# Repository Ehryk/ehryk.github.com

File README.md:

ehryk.github.com
================

This is my github pages repo, viewable at [ehryk.github.io](http://ehryk.github.io). It also has some setup files that I sync between various computers, most notably git and bash aliases.

**Github Pages (/, /js, /css, /img)**

 - xkcd 1288 Substitutions Bookmarklet

**/linux && /git**

These are the settings I sync between various computers. Update Config.bat for windows, update-config.sh for linux.

**/rainmeter**

Custom Rainmeter skins for GPU and CPU temps, etc.

**/brian**

Brian's Stuff. See more at [Dr. Bird.org](http://www.drbird.org/)

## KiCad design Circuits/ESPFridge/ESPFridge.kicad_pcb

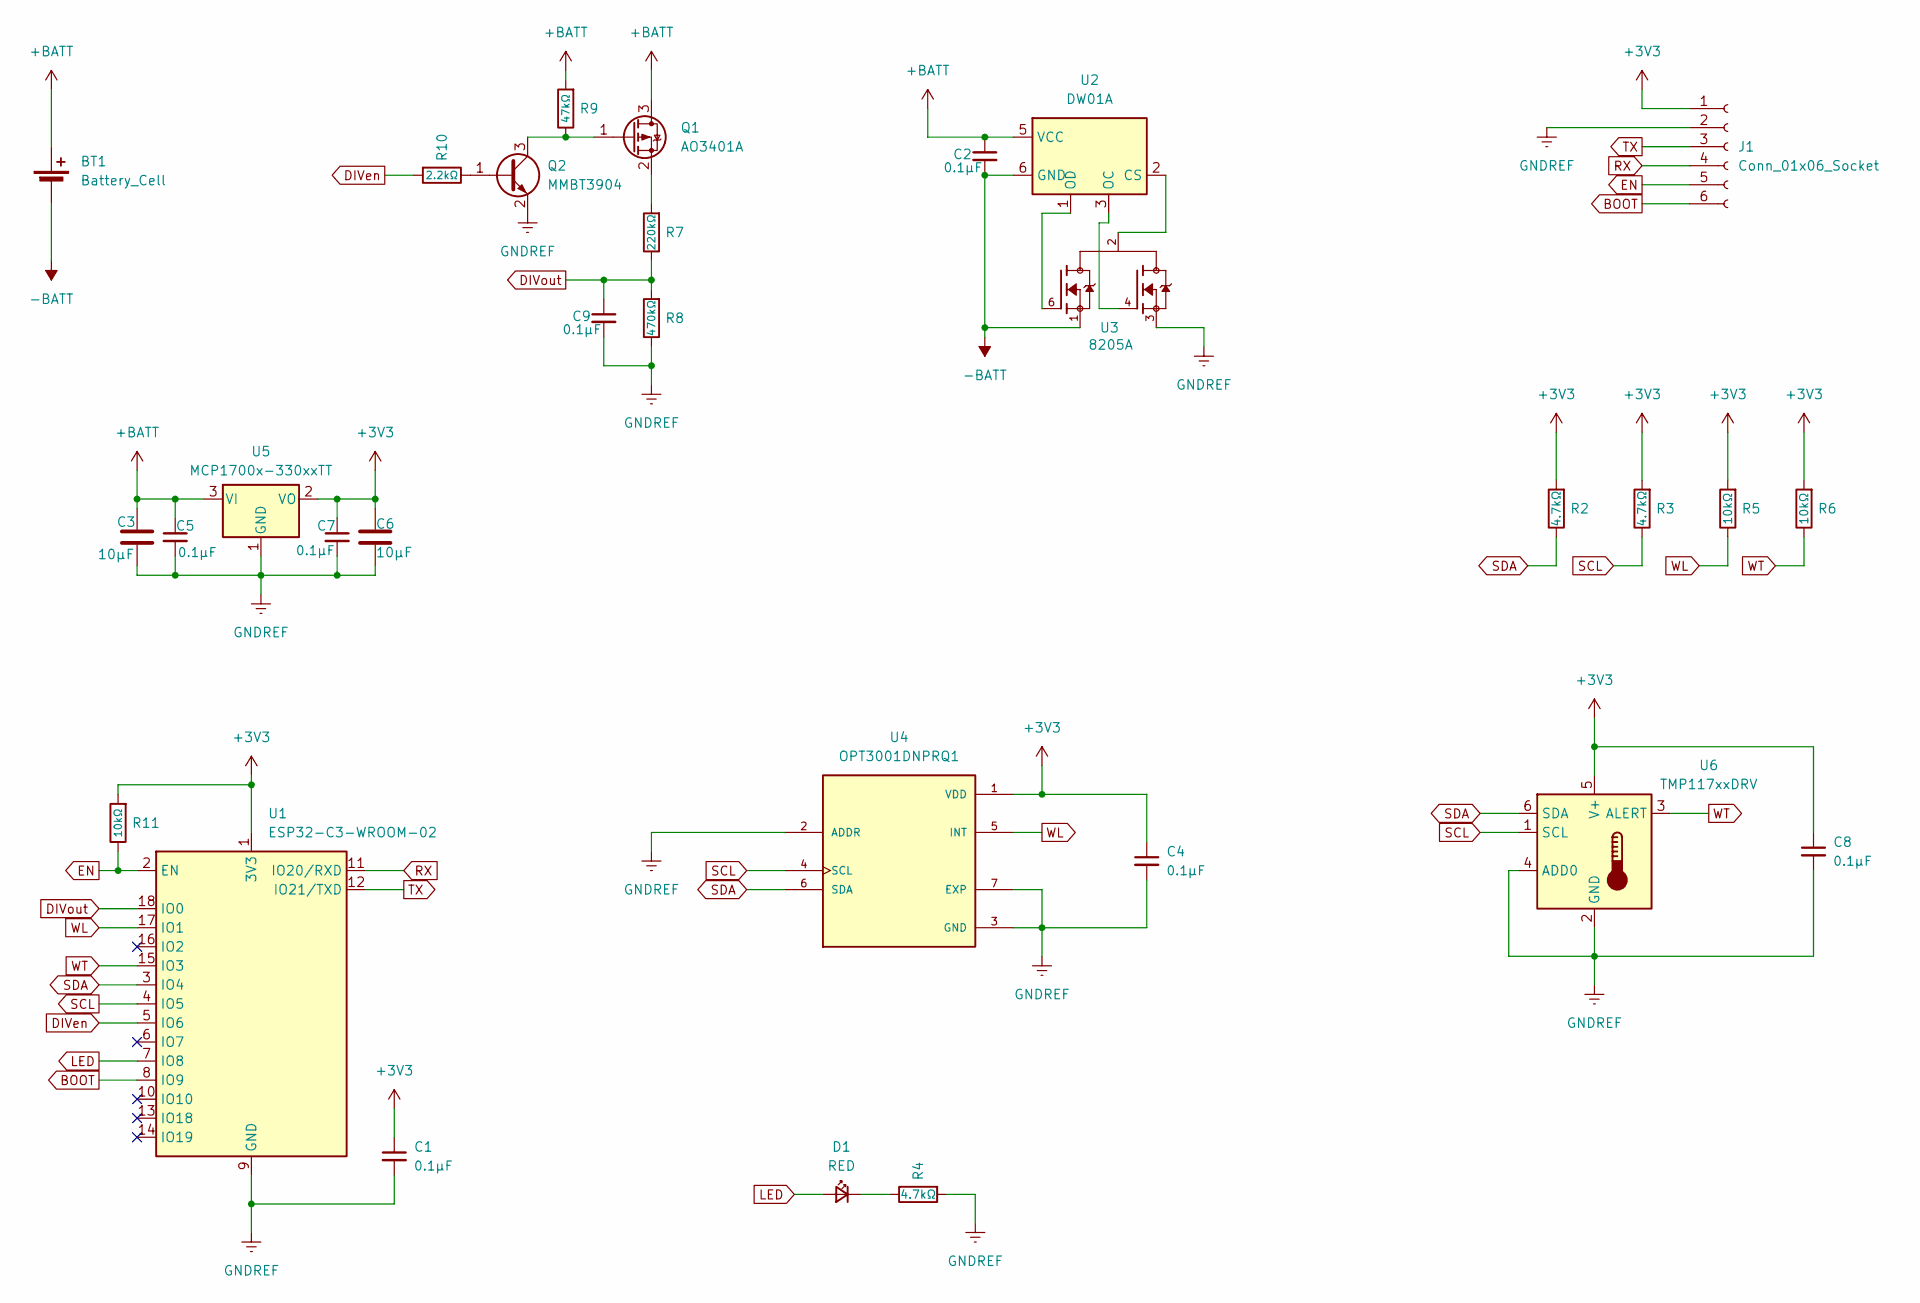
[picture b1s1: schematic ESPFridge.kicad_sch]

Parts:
BT1: Battery_Cell; Keystone_1043
C1, C2, C4, C5, C7, C8, C9: 0.1µF; C_1206_3216Metric_Pad1.33x1.80mm_HandSolder
C3, C6: 10µF; C_1210_3225Metric_Pad1.33x2.70mm_HandSolder
D1: RED; LED_0805_2012Metric_Pad1.15x1.40mm_HandSolder
J1: Conn_01x06_Socket; PinSocket_1x06_P2.00mm_Vertical_SMD_Pin1Left
Q1: AO3401A; SOT-23
Q2: MMBT3904; SOT-23
R2, R3, R4: 4.7kΩ; R_0805_2012Metric_Pad1.20x1.40mm_HandSolder
R5, R6, R11: 10kΩ; R_0805_2012Metric_Pad1.20x1.40mm_HandSolder
R7: 220kΩ; R_0805_2012Metric_Pad1.20x1.40mm_HandSolder
R8: 470kΩ; R_0805_2012Metric_Pad1.20x1.40mm_HandSolder
R9: 47kΩ; R_0805_2012Metric_Pad1.20x1.40mm_HandSolder
R10: 2.2kΩ; R_0805_2012Metric_Pad1.20x1.40mm_HandSolder
U1: ESP32-C3-WROOM-02
U2: DW01A; SOT-23-6
U3: 8205A; SOT95P285X140-6N; PARTREV NA
U4: OPT3001DNPRQ1; SON65P200X200X65-7N; PARTREV 01/2018
U5: MCP1700x-330xxTT; SOT-23
U6: TMP117xxDRV; WSON-6-1EP_2x2mm_P0.65mm_EP1x1.6mm

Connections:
+3V3: C1.1, C4.1, C6.1, C7.1, C8.1, J1.1, R2.2, R3.2, R5.2, R6.2, R11.2, U1.1 (3V3), U4.1 (VDD), U5.2 (VO), U6.5 (V+)
+BATT: BT1.P (+), C2.1, C3.1, C5.1, Q1.3 (D), R9.2, U2.5 (VCC), U5.3 (VI)
-BATT: BT1.N (-), C2.2, U2.6 (GND), U3.1
BOOT: J1.6, U1.8 (IO9)
DIVen: R10.2, U1.5 (IO6)
DIVout: C9.1, R7.1, R8.2, U1.18 (IO0)
EN: J1.5, R11.1, U1.2 (EN)
GNDREF: C1.2, C3.2, C4.2, C5.2, C6.2, C7.2, C8.2, C9.2, J1.2, Q2.2 (E), R4.2, R8.1, U1.9 (GND), U1.19 (GND), U3.3, U4.2 (ADDR), U4.3 (GND), U4.7 (EXP), U5.1 (GND), U6.2 (GND), U6.4 (ADD0)
LED: D1.2 (A), U1.7 (IO8)
unnamed: D1.1 (K), R4.1
unnamed: Q1.1 (G), Q2.3 (C), R9.1
unnamed: Q1.2 (S), R7.2
unnamed: Q2.1 (B), R10.1
unnamed: U2.2 (CS), U3.2, U3.5
unnamed: U2.3 (OC), U3.4
unnamed: U2.1 (OD), U3.6
RX: J1.4, U1.11 (IO20/RXD)
SCL: R3.1, U1.4 (IO5), U4.4 (SCL), U6.1 (SCL)
SDA: R2.1, U1.3 (IO4), U4.6 (SDA), U6.6 (SDA)
TX: J1.3, U1.12 (IO21/TXD)
WL: R5.1, U1.17 (IO1), U4.5 (INT)
WT: R6.1, U1.15 (IO3), U6.3 (ALERT)

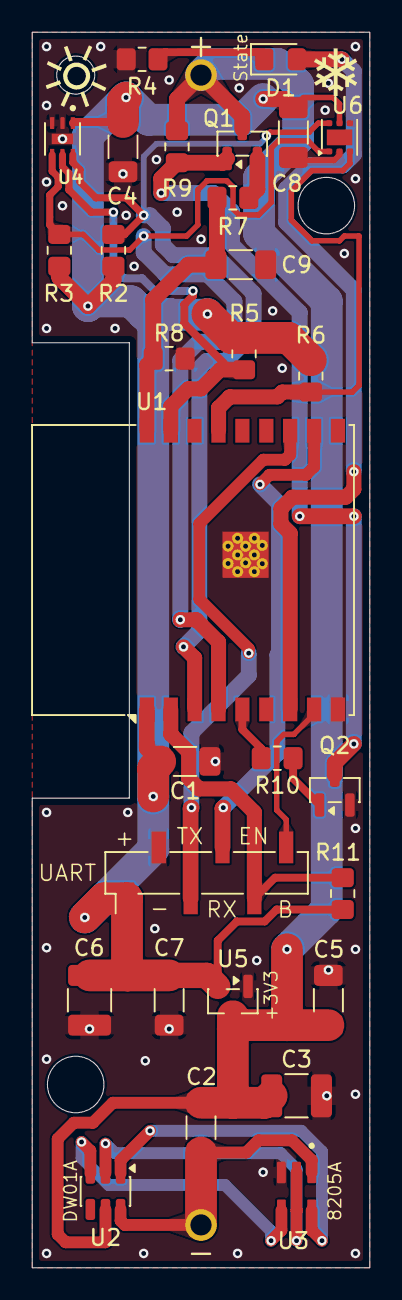
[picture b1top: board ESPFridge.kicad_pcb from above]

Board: 2 copper layers, 21.2 x 77.6 mm, 30 parts (1 on the bottom side), 22 nets.

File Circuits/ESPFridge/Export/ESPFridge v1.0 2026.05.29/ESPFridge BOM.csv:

"Reference","Qty","Value","DNP","Exclude from BOM","Exclude from Board","Footprint","Datasheet","#"
"BT1","1","Battery_Cell","","","","Ehryk:Keystone_1043","","1"
"C1,C2,C4,C5,C7,C8,C9","7","0.1µF","","","","Capacitor_SMD:C_1206_3216Metric_Pad1.33x1.80mm_HandSolder","","2"
"C3,C6","2","10µF","","","","Capacitor_SMD:C_1210_3225Metric_Pad1.33x2.70mm_HandSolder","","3"
"D1","1","RED","","","","LED_SMD:LED_0805_2012Metric_Pad1.15x1.40mm_HandSolder","","4"
"J1","1","Conn_01x06_Socket","","","","Connector_PinSocket_2.00mm:PinSocket_1x06_P2.00mm_Vertical_SMD_Pin1Left","","5"
"Q1","1","AO3401A","","","","Package_TO_SOT_SMD:SOT-23","http://www.aosmd.com/pdfs/datasheet/AO3401A.pdf","6"
"Q2","1","MMBT3904","","","","Package_TO_SOT_SMD:SOT-23","https://www.onsemi.com/pdf/datasheet/pzt3904-d.pdf","7"
"R2,R3,R4","3","4.7kΩ","","","","Resistor_SMD:R_0805_2012Metric_Pad1.20x1.40mm_HandSolder","","8"
"R5,R6,R11","3","10kΩ","","","","Resistor_SMD:R_0805_2012Metric_Pad1.20x1.40mm_HandSolder","","9"
"R7","1","220kΩ","","","","Resistor_SMD:R_0805_2012Metric_Pad1.20x1.40mm_HandSolder","","10"
"R8","1","470kΩ","","","","Resistor_SMD:R_0805_2012Metric_Pad1.20x1.40mm_HandSolder","","11"
"R9","1","47kΩ","","","","Resistor_SMD:R_0805_2012Metric_Pad1.20x1.40mm_HandSolder","","12"
"R10","1","2.2kΩ","","","","Resistor_SMD:R_0805_2012Metric_Pad1.20x1.40mm_HandSolder","","13"
"U1","1","ESP32-C3-WROOM-02","","","","RF_Module:ESP32-C3-WROOM-02","https://www.espressif.com/sites/default/files/documentation/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","14"
"U2","1","DW01A","","","","Package_TO_SOT_SMD:SOT-23-6","https://hmsemi.com/downfile/DW01A.PDF","15"
"U3","1","8205A","","","","Ehryk:SOT95P285X140-6N","","16"
"U4","1","OPT3001DNPRQ1","","","","Ehryk:SON65P200X200X65-7N","","17"
"U5","1","MCP1700x-330xxTT","","","","Package_TO_SOT_SMD:SOT-23","http://ww1.microchip.com/downloads/en/DeviceDoc/20001826D.pdf","18"
"U6","1","TMP117xxDRV","","","","Package_SON:WSON-6-1EP_2x2mm_P0.65mm_EP1x1.6mm","https://www.ti.com/lit/ds/symlink/tmp117.pdf","19"

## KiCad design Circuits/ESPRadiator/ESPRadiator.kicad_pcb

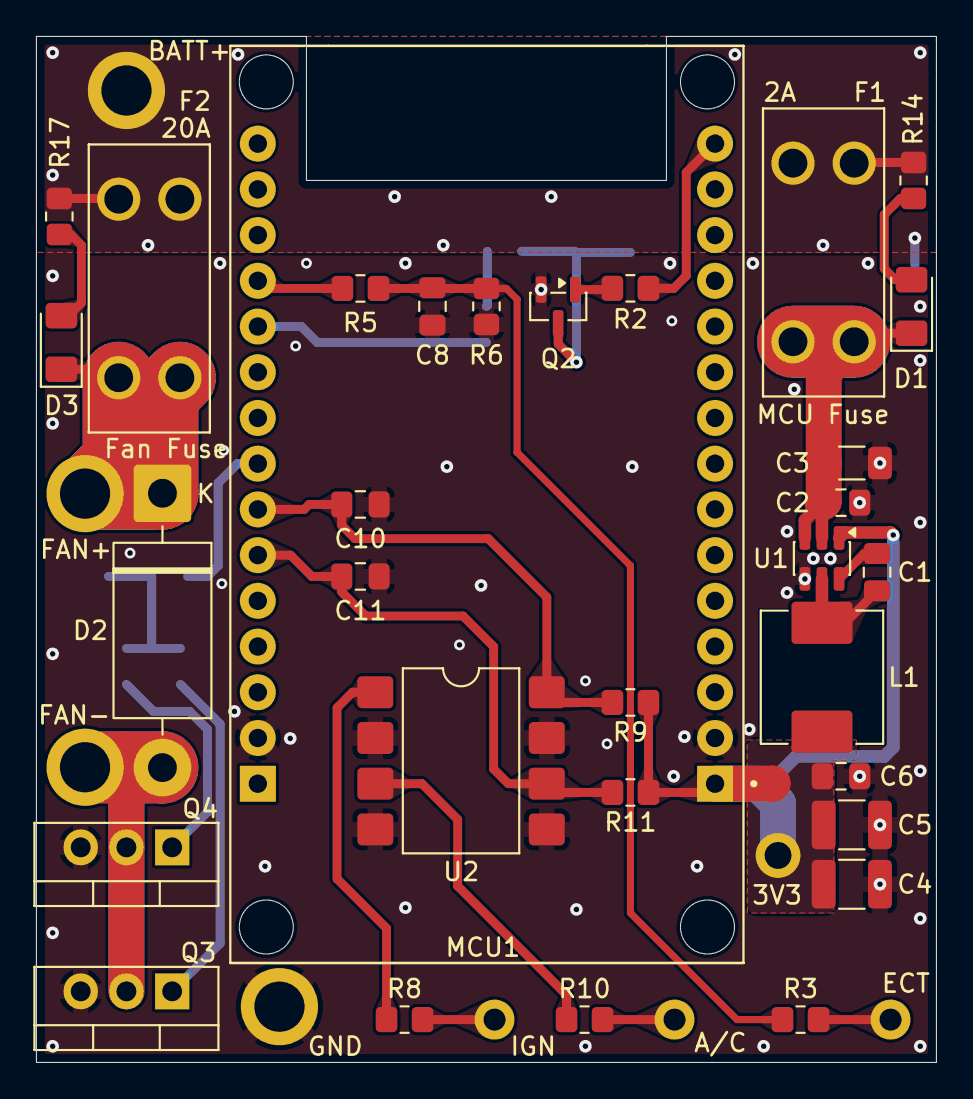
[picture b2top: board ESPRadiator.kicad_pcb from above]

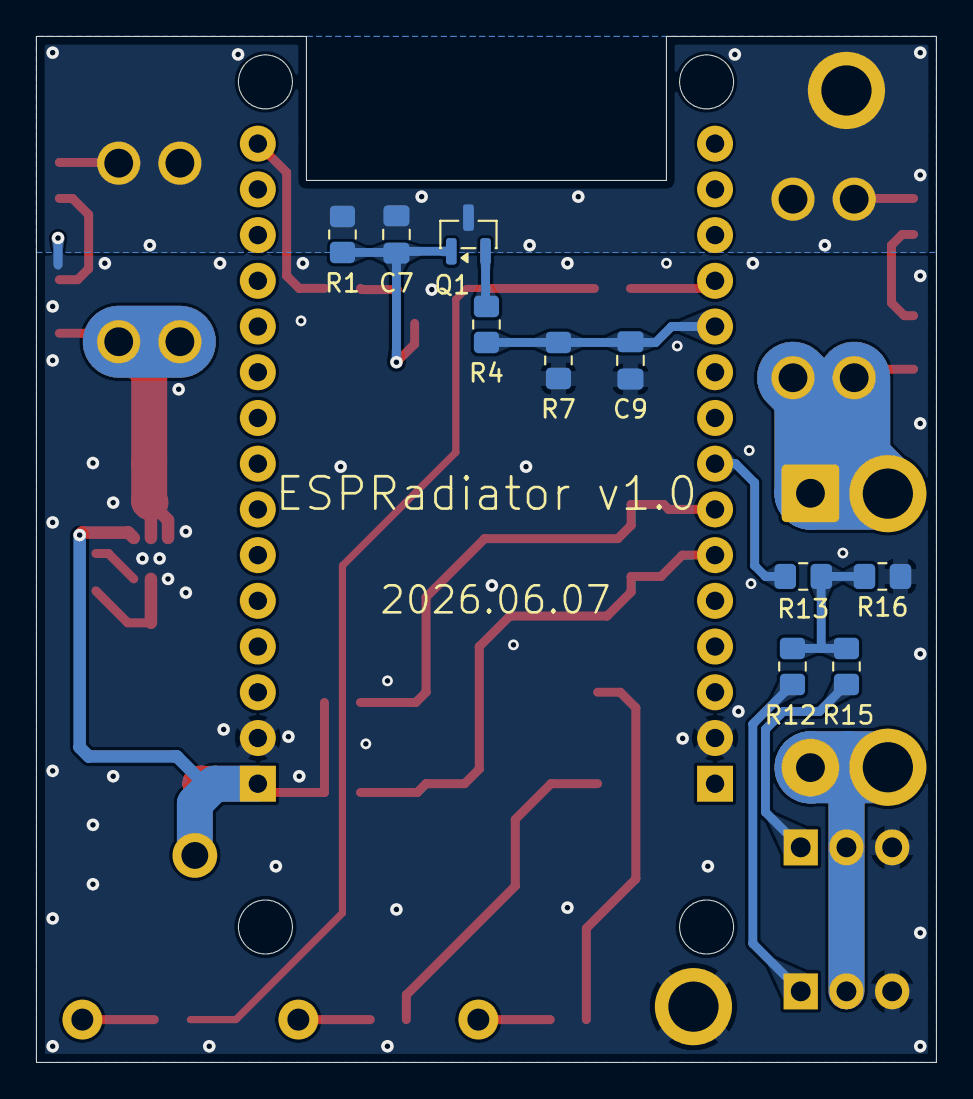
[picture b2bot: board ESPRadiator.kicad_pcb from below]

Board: 2 copper layers, 50.0 x 57.0 mm, 49 parts (10 on the bottom side), 28 nets.

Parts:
C1, C2, C6, C7, C8, C9, C10, C11: 0.1μF; C_0805_2012Metric_Pad1.18x1.45mm_HandSolder
C3: 10μF; C_1206_3216Metric_Pad1.33x1.80mm_HandSolder
C4, C5: 22μF; C_1210_3225Metric_Pad1.33x2.70mm_HandSolder
D1, D3: LED; LED_1206_3216Metric_Pad1.42x1.75mm_HandSolder
D2: 1N5822; D_DO-201AD_P15.24mm_Horizontal
F1, F2: 3568; FUSE_3568
L1: 6.8μH; L_Abracon_ASPI-0630LR
MCU1: ESP32-DEVKIT-V1; ESP32_DEVKIT_V1
Q1: AO3401A; SOT-23
Q2: MMBT3904; SOT-23
Q3, Q4: IRLZ44N; TO-220-3_Vertical
R1, R3, R9, R11, R16: 10kΩ; R_0805_2012Metric_Pad1.20x1.40mm_HandSolder
R2, R5: 4.7kΩ; R_0805_2012Metric_Pad1.20x1.40mm_HandSolder
R4: 150kΩ; R_0805_2012Metric_Pad1.20x1.40mm_HandSolder
R6: 15kΩ; R_0805_2012Metric_Pad1.20x1.40mm_HandSolder
R7: 27kΩ; R_0805_2012Metric_Pad1.20x1.40mm_HandSolder
R8, R10, R14, R17: 1kΩ; R_0805_2012Metric_Pad1.20x1.40mm_HandSolder
R12, R15: 10Ω; R_0805_2012Metric_Pad1.20x1.40mm_HandSolder
R13: 220Ω; R_0805_2012Metric_Pad1.20x1.40mm_HandSolder
U1: AP63203WU; TSOT-23-6
U2: LTV-827S; SMDIP-8_W9.53mm
W1: V+; WIRE-10AWG
W2: 3V3; WIRE-16AWG
W3: V-; WIRE-10AWG
W4: FAN+; WIRE-10AWG
W5: FAN-; WIRE-10AWG
W6: ECT; WIRE-18AWG
W7: IGN; WIRE-18AWG
W8: AC; WIRE-18AWG

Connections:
+3V3: C4.2, C5.2, C6.1, L1.2, MCU1.16 (3V3), R9.1, R11.1, U1.1 (FB), W2.1
+BATT: C7.1, F1.1, F1.3, F2.1, F2.3, Q1.3 (D), R1.2, R14.1, R17.1, W1.1
+BATTfused: C2.1, C3.2, D1.1 (K), F1.2, F1.4, U1.2 (EN), U1.3 (IN)
+FANfused: D2.1 (K), D3.1 (K), F2.2, F2.4, W4.1
ACraw: R10.1, W8.1
ACsense: C11.1, MCU1.10 (D27), R11.2, U2.6
BATTsense: C9.1, MCU1.5 (D35), R4.1, R7.2
BATTsenseEN: MCU1.30 (D23), R2.1
ECTraw: R3.2, W6.1
ECTsense: MCU1.4 (D34), R5.1
FAN-: D2.2 (A), Q3.2 (D), Q4.2 (D), W5.1
FANpwm: MCU1.8 (D25), R13.1
GNDREF: C2.2, C3.1, C4.1, C5.1, C6.2, C8.2, C9.2, C10.2, C11.2, MCU1.14 (GND), MCU1.17 (GND), Q2.2 (E), Q3.3 (S), Q4.3 (S), R6.1, R7.1, R16.1, U1.4 (GND), U2.2, U2.4, U2.5, U2.7, W3.1
IGNraw: R8.1, W7.1
IGNsense: C10.1, MCU1.9 (D26), R9.2, U2.8
unnamed: C8.1, R3.1, R5.2, R6.2
unnamed: D1.2 (A), R14.2
unnamed: D3.2 (A), R17.2
unnamed: C7.2, Q1.1 (G), Q2.3 (C), R1.1
unnamed: Q1.2 (S), R4.2
unnamed: Q2.1 (B), R2.2
unnamed: Q3.1 (G), R12.2
unnamed: Q4.1 (G), R15.2
unnamed: R8.2, U2.1
unnamed: R10.2, U2.3
unnamed: R12.1, R13.2, R15.1, R16.2
unnamed: C1.1, U1.6 (BST)
unnamed: C1.2, L1.1, U1.5 (SW)

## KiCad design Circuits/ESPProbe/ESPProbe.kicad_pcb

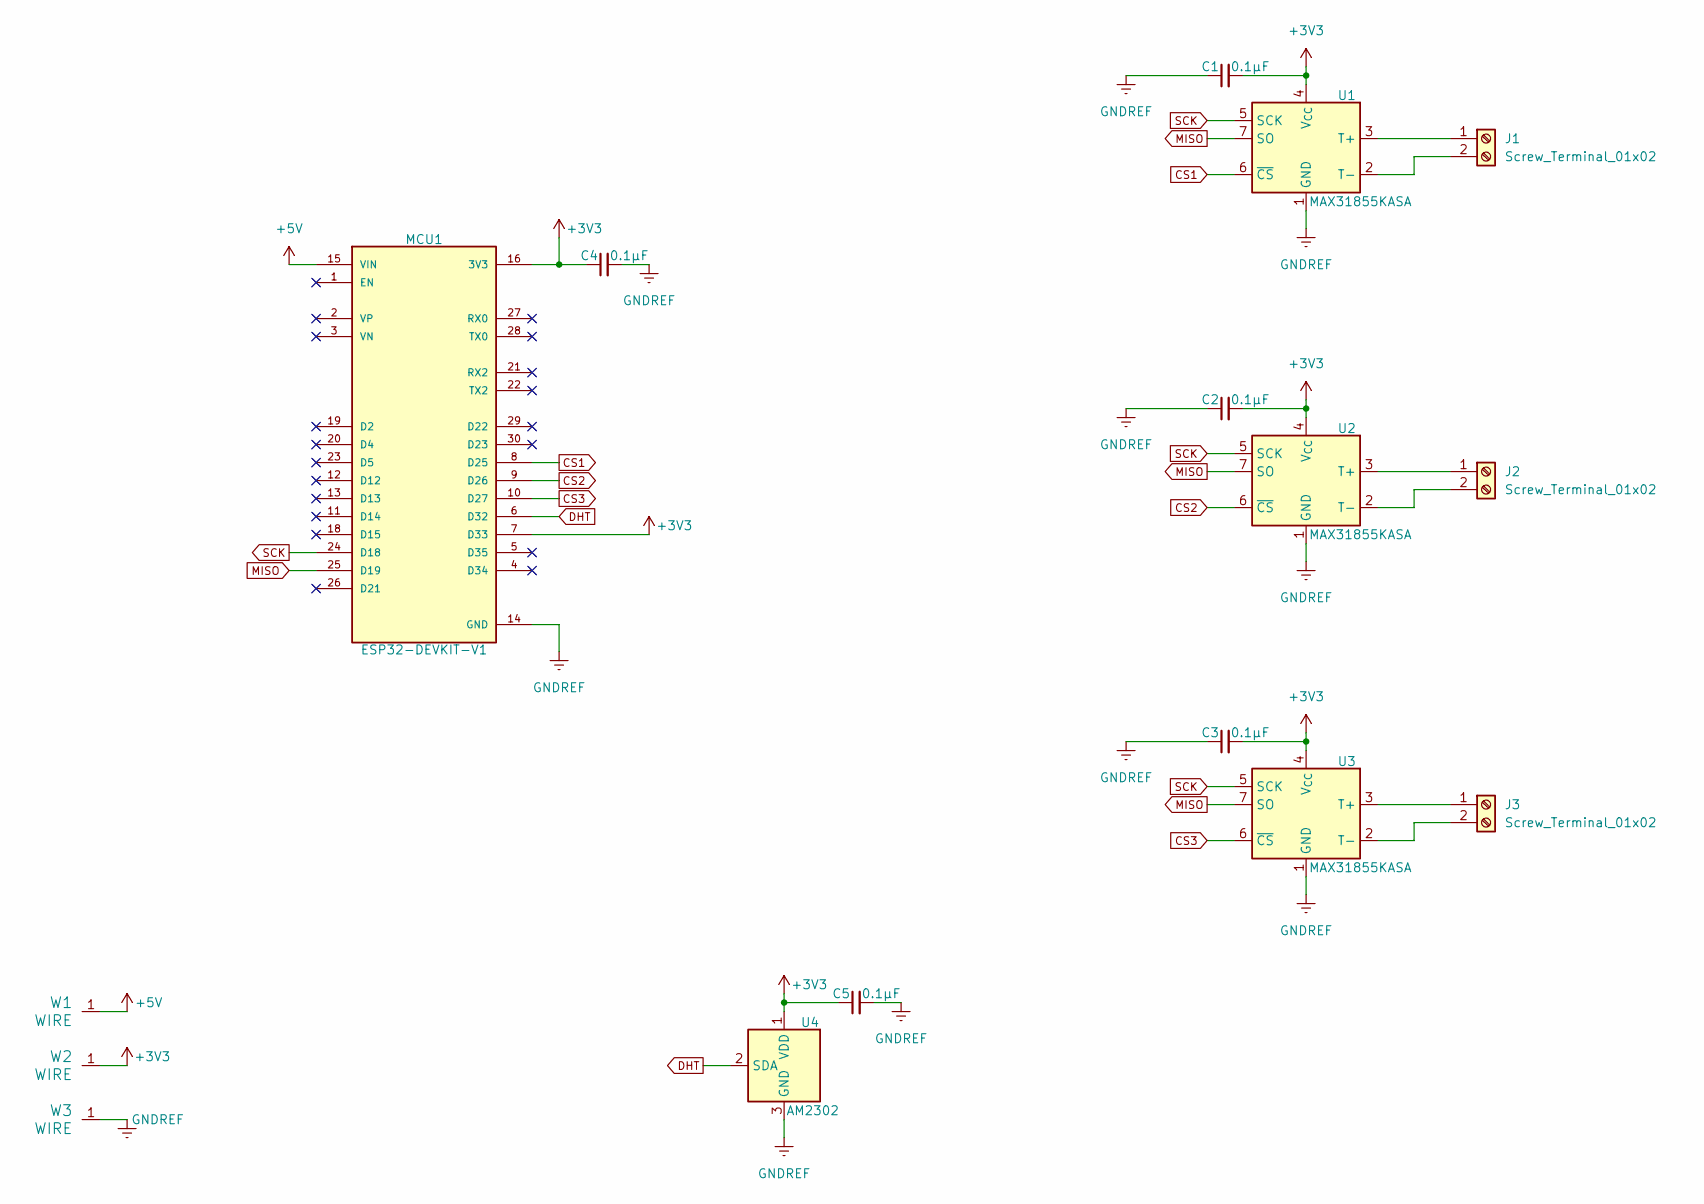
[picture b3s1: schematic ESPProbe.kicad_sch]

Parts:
C1, C2, C3, C4, C5: 0.1μF; C_1206_3216Metric_Pad1.33x1.80mm_HandSolder
J1, J2, J3: Screw_Terminal_01x02; TerminalBlock_CUI_TB007-508-02_1x02_P5.08mm_Horizontal
MCU1: ESP32-DEVKIT-V1; ESP32_DEVKIT_V1
U1, U2, U3: MAX31855KASA; SOIC-8_3.9x4.9mm_P1.27mm
U4: AM2302; ASAIR_AM2302_P2.54mm_Vertical
W1, W2, W3: WIRE; WIRE-18AWG

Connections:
+3V3: C1.2, C2.2, C3.2, C4.1, C5.1, MCU1.7 (D33), MCU1.16 (3V3), U1.4 (V_{CC}), U2.4 (V_{CC}), U3.4 (V_{CC}), U4.1 (VDD), W2.1
+5V: MCU1.15 (VIN), W1.1
CS1: MCU1.8 (D25), U1.6 (~CS)
CS2: MCU1.9 (D26), U2.6 (~CS)
CS3: MCU1.10 (D27), U3.6 (~CS)
DHT: MCU1.6 (D32), U4.2 (SDA)
GNDREF: C1.1, C2.1, C3.1, C4.2, C5.2, MCU1.14 (GND), MCU1.17 (GND), U1.1 (GND), U2.1 (GND), U3.1 (GND), U4.3 (GND), U4.4 (GND), W3.1
MISO: MCU1.25 (D19), U1.7 (SO), U2.7 (SO), U3.7 (SO)
unnamed: J1.1, U1.3 (T+)
unnamed: J1.2, U1.2 (T-)
unnamed: J2.1, U2.3 (T+)
unnamed: J2.2, U2.2 (T-)
unnamed: J3.1, U3.3 (T+)
unnamed: J3.2, U3.2 (T-)
SCK: MCU1.24 (D18), U1.5 (SCK), U2.5 (SCK), U3.5 (SCK)

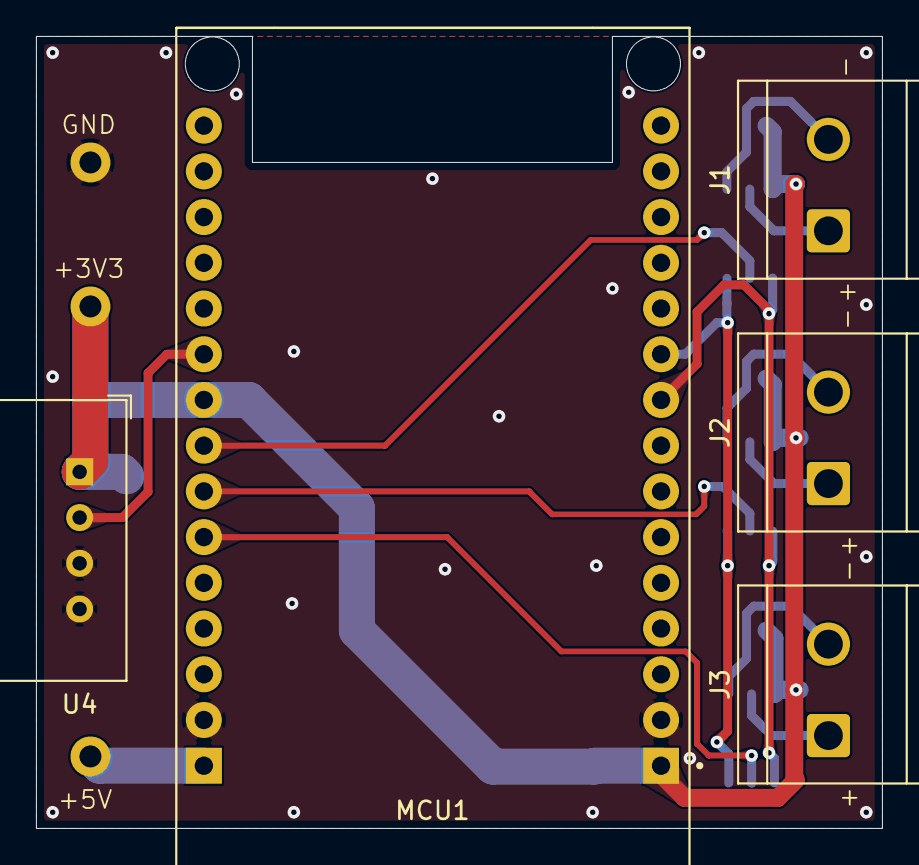
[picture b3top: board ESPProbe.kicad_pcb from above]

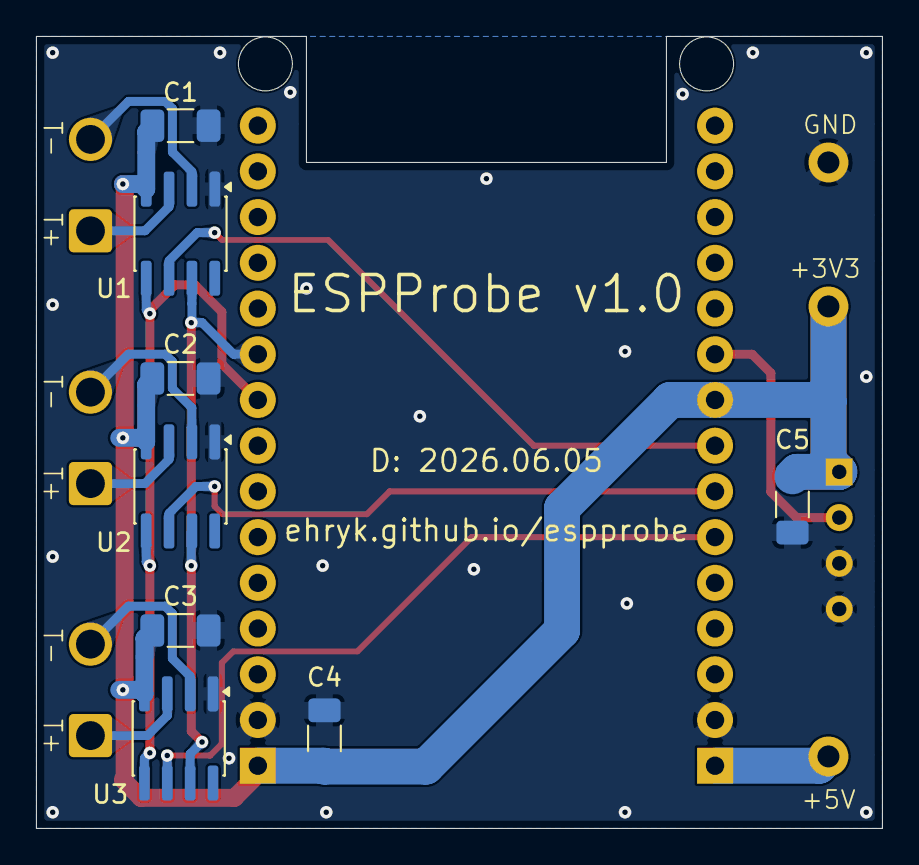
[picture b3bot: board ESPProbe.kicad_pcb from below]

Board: 2 copper layers, 47.0 x 44.0 mm, 16 parts (8 on the bottom side), 15 nets.

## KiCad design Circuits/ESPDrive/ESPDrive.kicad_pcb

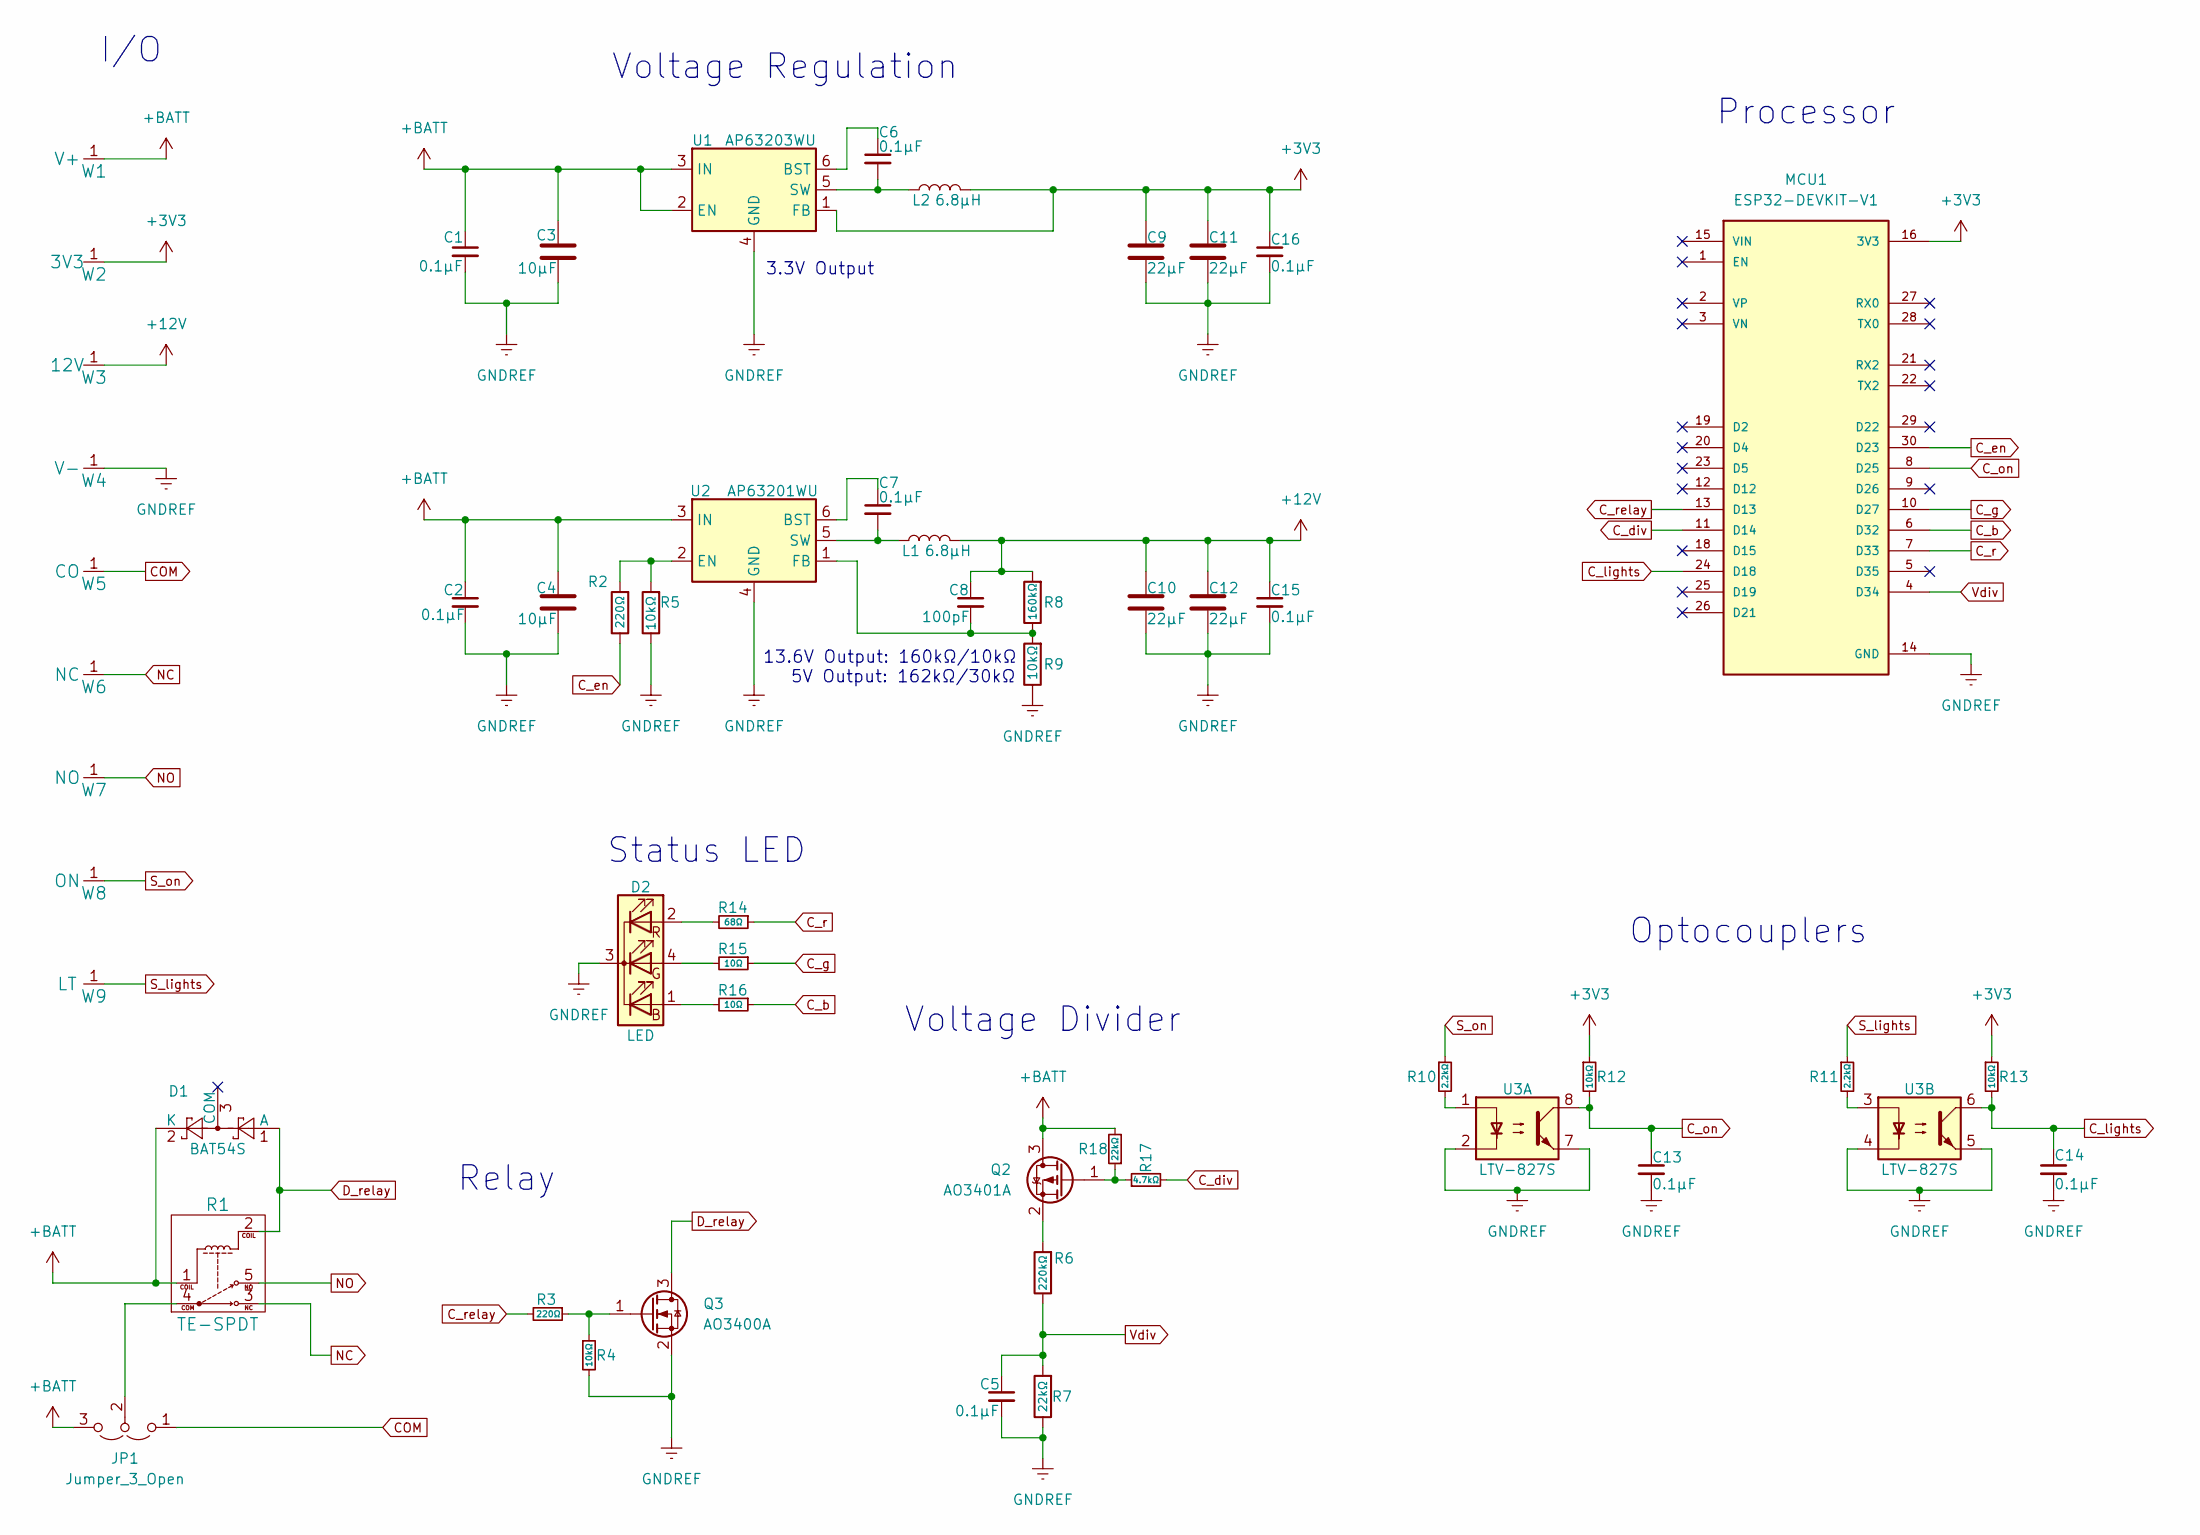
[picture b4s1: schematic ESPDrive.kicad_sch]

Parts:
C1, C2, C5, C6, C7, C13, C14, C15, C16: 0.1μF; C_0805_2012Metric_Pad1.18x1.45mm_HandSolder
C3, C4: 10μF; C_1206_3216Metric_Pad1.33x1.80mm_HandSolder
C8: 100pF; C_0805_2012Metric_Pad1.18x1.45mm_HandSolder
C9, C10, C11, C12: 22μF; C_1210_3225Metric_Pad1.33x2.70mm_HandSolder
D1: BAT54S; SOT-23
D2: LED; PinHeader_1x04_P2.54mm_Vertical
JP1: Jumper_3_Open; PinHeader_1x03_P2.54mm_Vertical
L1, L2: 6.8μH; L_Abracon_ASPI-0630LR
MCU1: ESP32-DEVKIT-V1; ESP32_DEVKIT_V1
Q2: AO3401A; SOT-23
Q3: AO3400A; SOT-23
R1: TE-SPDT
R2, R3: 220Ω; R_0805_2012Metric_Pad1.20x1.40mm_HandSolder
R4, R5, R9, R12, R13: 10kΩ; R_0805_2012Metric_Pad1.20x1.40mm_HandSolder
R6: 220kΩ; R_0805_2012Metric_Pad1.20x1.40mm_HandSolder
R7, R18: 22kΩ; R_0805_2012Metric_Pad1.20x1.40mm_HandSolder
R8: 160kΩ; R_0805_2012Metric_Pad1.20x1.40mm_HandSolder
R10, R11: 2.2kΩ; R_0805_2012Metric_Pad1.20x1.40mm_HandSolder
R14: 68Ω; R_0805_2012Metric_Pad1.20x1.40mm_HandSolder
R15, R16: 10Ω; R_0805_2012Metric_Pad1.20x1.40mm_HandSolder
R17: 4.7kΩ; R_0805_2012Metric_Pad1.20x1.40mm_HandSolder
U1: AP63203WU; TSOT-23-6
U2: AP63201WU; TSOT-23-6
U3: LTV-827S; SMDIP-8_W9.53mm
W1: V+; WIRE-14AWG
W2: 3V3; WIRE-16AWG
W3: 12V; WIRE-16AWG
W4: V-; WIRE-14AWG
W5: CO; WIRE-14AWG
W6: NC; WIRE-14AWG
W7: NO; WIRE-14AWG
W8: ON; WIRE-18AWG
W9: LT; WIRE-18AWG

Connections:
+3V3: C9.2, C11.2, C16.1, L2.2, MCU1.16 (3V3), R12.1, R13.1, U1.1 (FB), W2.1
+12V: C8.1, C10.2, C12.2, C15.1, L1.2, R8.2, W3.1
+BATT: C1.1, C2.1, C3.2, C4.2, D1.2 (K), JP1.3 (B), Q2.3 (D), R1.1, R18.2, U1.2 (EN), U1.3 (IN), U2.3 (IN), W1.1
COM: JP1.1 (A), W5.1
C_b: MCU1.6 (D32), R16.1
C_div: MCU1.11 (D14), R17.2
C_en: MCU1.30 (D23), R2.1
C_g: MCU1.10 (D27), R15.1
C_lights: C14.1, MCU1.24 (D18), R13.2, U3.6
C_on: C13.1, MCU1.8 (D25), R12.2, U3.8
C_r: MCU1.7 (D33), R14.1
C_relay: MCU1.13 (D13), R3.2
D_relay: D1.1 (A), Q3.3 (D), R1.2
GNDREF: C1.2, C2.2, C3.1, C4.1, C5.2, C9.1, C10.1, C11.1, C12.1, C13.2, C14.2, C15.2, C16.2, D2.3 (K), MCU1.14 (GND), MCU1.17 (GND), Q3.2 (S), R4.2, R5.1, R7.1, R9.1, U1.4 (GND), U2.4 (GND), U3.2, U3.4, U3.5, U3.7, W4.1
NC: R1.3, W6.1
NO: R1.5, W7.1
unnamed: D2.1 (BA), R16.2
unnamed: D2.4 (GA), R15.2
unnamed: D2.2 (RA), R14.2
unnamed: JP1.2 (C), R1.4
unnamed: Q2.1 (G), R17.1, R18.1
unnamed: Q2.2 (S), R6.2
unnamed: Q3.1 (G), R3.1, R4.1
unnamed: R10.2, U3.1
unnamed: R11.2, U3.3
unnamed: C6.1, U1.6 (BST)
unnamed: C6.2, L2.1, U1.5 (SW)
unnamed: C7.1, U2.6 (BST)
unnamed: R2.2, R5.2, U2.2 (EN)
unnamed: C8.2, R8.1, R9.2, U2.1 (FB)
unnamed: C7.2, L1.1, U2.5 (SW)
S_lights: R11.1, W9.1
S_on: R10.1, W8.1
Vdiv: C5.1, MCU1.4 (D34), R6.1, R7.2

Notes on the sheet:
I/O
Processor
Optocouplers
3.3V Output
Voltage Regulation
13.6V Output: 160kΩ/10kΩ 5V Output: 162kΩ/30kΩ
Voltage Divider
Relay
Status LED

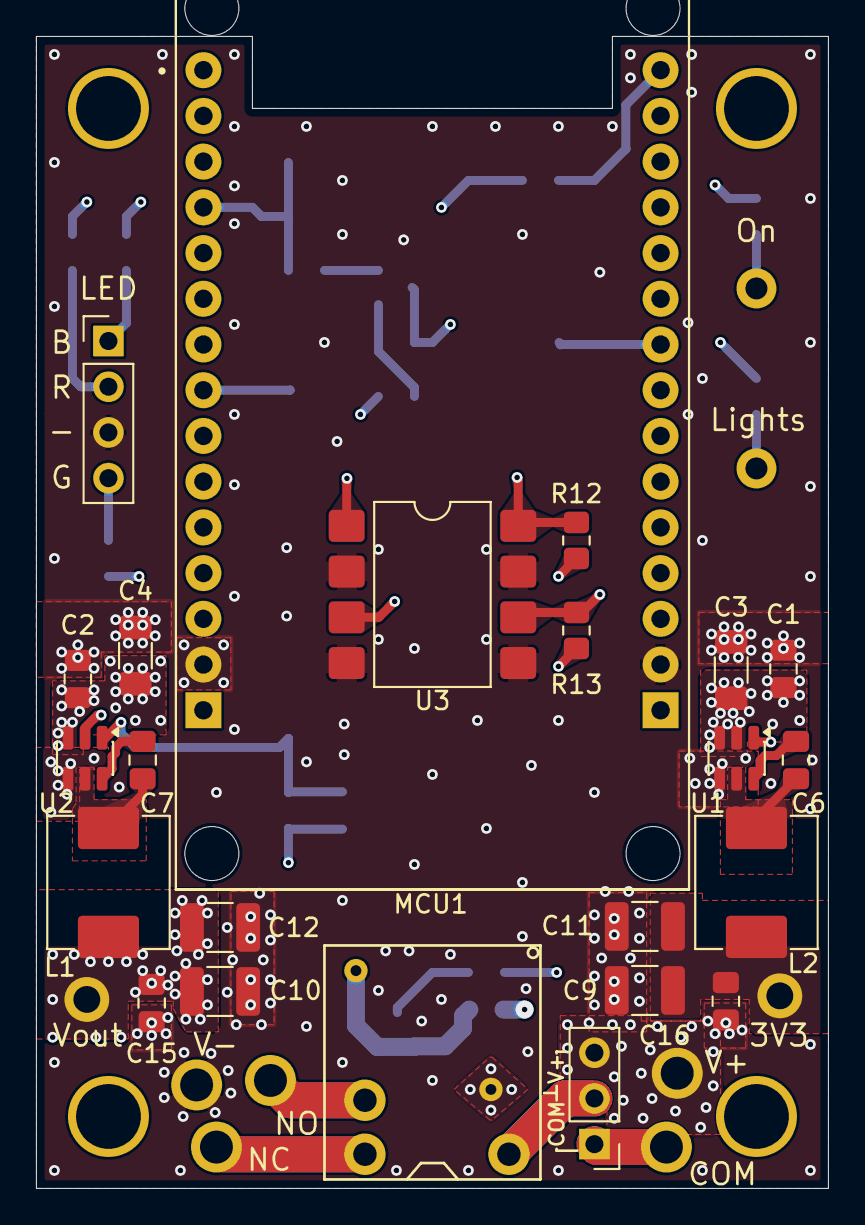
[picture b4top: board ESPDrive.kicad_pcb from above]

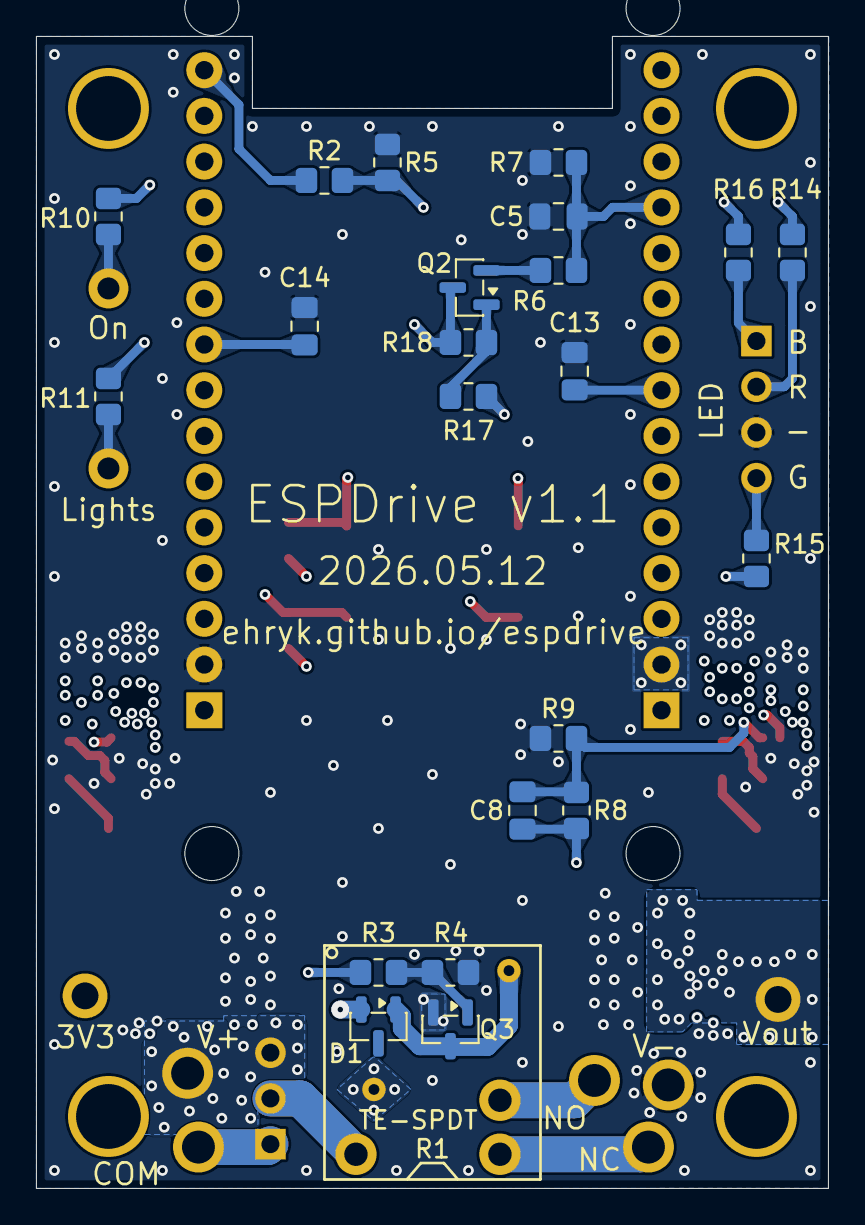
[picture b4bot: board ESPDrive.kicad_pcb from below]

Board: 4 copper layers, 44.0 x 64.0 mm, 58 parts (22 on the bottom side), 34 nets.

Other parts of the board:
Ref**: Val**; 6-32UNC_Screw_Hole
Ref**#2, Ref**#3, Ref**#4: Val**; 6-32UNC_Screw_Hole

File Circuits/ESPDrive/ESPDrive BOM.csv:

Reference,Value,Datasheet,Footprint,Qty,DNP,#,Ordered,Part Number,Brand
"C1,C2,C5,C6,C7,C13,C14,C15,C16",0.1μF,,Capacitor_SMD:C_0805_2012Metric_Pad1.18x1.45mm_HandSolder,9,,1,100,AC0805KRX7R9BB104 ,YAGEO 
"C3,C4",10μF,,Capacitor_SMD:C_1206_3216Metric_Pad1.33x1.80mm_HandSolder,2,,2,50,CL32B226KAJNNNE ,Samsung Electro-Mechanics 
C8,100pF,,Capacitor_SMD:C_0805_2012Metric_Pad1.18x1.45mm_HandSolder,1,,3,10,C0805C101J5GACTU ,KEMET 
"C9,C10,C11,C12",22μF,,Capacitor_SMD:C_1210_3225Metric_Pad1.33x2.70mm_HandSolder,4,,4,50,CL31B106KBHNNNE ,Samsung Electro-Mechanics 
D1,BAT54S,https://www.diodes.com/assets/Datasheets/ds11005.pdf,Package_TO_SOT_SMD:SOT-23,1,,5,10,BAT54SFILM ,STMicroelectronics 
D2,LED,,Connector_PinHeader_2.54mm:PinHeader_1x04_P2.54mm_Vertical,1,,6,10,INL-5TB4URGB60 ,Inolux 
D2,,,,1,,6,10,SSH-LXH501 ,Lumex Opto/Components Inc. 
"L1,L2",6.8μH,,Inductor_SMD:L_TechFuse_SL0630,2,,7,25,ASPI-0630LR-6R8M-T15 ,Abracon LLC
MCU1,ESP32-DEVKIT-V1,,Ehryk:ESP32_DEVKIT_V1,1,,8,,,
Q1,‎AO3400A‎ ,https://www.aosmd.com/res/datasheets/AOSS32334C.pdf,Package_TO_SOT_SMD:SOT-23-3,1,,9,10,‎AO3400A‎ ,UMW
R1,TE-SPDT,,Ehryk:TE-SPDT,1,,10,,,
"R2,R3",220Ω,,Resistor_SMD:R_0805_2012Metric_Pad1.20x1.40mm_HandSolder,2,,11,25,CRGCQ0805F220R ,TE Connectivity Passive Product 
"R4,R5,R12,R13",10kΩ,,Resistor_SMD:R_0805_2012Metric_Pad1.20x1.40mm_HandSolder,4,,12,50,CRGCQ0805F10K ,TE Connectivity Passive Product 
R6,220kΩ,,Resistor_SMD:R_0805_2012Metric_Pad1.20x1.40mm_HandSolder,1,,13,10,CRGCQ0805F220K ,TE Connectivity Passive Product 
R7,22kΩ,,Resistor_SMD:R_0805_2012Metric_Pad1.20x1.40mm_HandSolder,1,,14,10,CRGCQ0805F22K ,TE Connectivity Passive Product 
R8,160kΩ,,Resistor_SMD:R_0805_2012Metric_Pad1.20x1.40mm_HandSolder,1,,15,10,RNCF0805DTE160K ,Stackpole Electronics Inc 
R8_Alt,162kΩ,,Resistor_SMD:R_0805_2012Metric_Pad1.20x1.40mm_HandSolder,1,,15,10,ERJ-PB6D1623V ,Panasonic Industry 
R9,10kΩ,,Resistor_SMD:R_0805_2012Metric_Pad1.20x1.40mm_HandSolder,1,,30,10,RNCF0805DTE10K0 ,Stackpole Electronics Inc 
R9_Alt,30kΩ,,Resistor_SMD:R_0805_2012Metric_Pad1.20x1.40mm_HandSolder,1,,30,10,RNCF0805DTE30K0 ,Stackpole Electronics Inc 
"R10,R11",2.7kΩ,,Resistor_SMD:R_0805_2012Metric_Pad1.20x1.40mm_HandSolder,2,,16,25,CRGCQ0805F2K7 ,TE Connectivity Passive Product 
R14,68Ω,,Resistor_SMD:R_0805_2012Metric_Pad1.20x1.40mm_HandSolder,1,,31,10,CRGCQ0805F68R‎ ,TE Connectivity Passive Product 
"R15,R16",10Ω,,Resistor_SMD:R_0805_2012Metric_Pad1.20x1.40mm_HandSolder,2,,17,25,CRGCQ0805F10R‎ ,TE Connectivity Passive Product 
U1,AP63203WU,https://www.diodes.com/assets/Datasheets/AP63200-AP63201-AP6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,Package_TO_SOT_SMD:TSOT-23-6,1,,18,10,AP63203QWU-7 ,Diodes Incorporated 
U2,AP63201WU,https://www.diodes.com/assets/Datasheets/AP63200-AP63201-AP6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,Package_TO_SOT_SMD:TSOT-23-6,1,,19,10,AP63201QWU-7 ,Diodes Incorporated 
U3,LTV-827S,http://www.us.liteon.com/downloads/LTV-817-827-847.PDF,Package_DIP:SMDIP-8_W9.53mm,1,,20,10,LTV-827S-TA1 ,LITEON 
W1,V+,,Ehryk:WIRE-14AWG,1,,21,,,
W2,3V3,,Ehryk:WIRE-16AWG,1,,22,,,
W3,12V,,Ehryk:WIRE-16AWG,1,,23,,,
W4,V-,,Ehryk:WIRE-14AWG,1,,24,,,
W5,CO,,Ehryk:WIRE-14AWG,1,,25,,,
W6,NC,,Ehryk:WIRE-14AWG,1,,26,,,
W7,NO,,Ehryk:WIRE-14AWG,1,,27,,,
W8,ON,,Ehryk:WIRE-18AWG,1,,28,,,
W9,LT,,Ehryk:WIRE-18AWG,1,,29,,,
